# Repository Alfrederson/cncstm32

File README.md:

# cncstm32
CNC Base for Blue Pill

To be used with this port of GRBL for STM32F103F8T6: https://github.com/usbcnc/grbl or with Yaroslav's bugfixed and improved version:
https://github.com/yaroslavVl/6-AXIS-USBCNC-GRBL .

This board works with either 3d printer drivers or with external drivers using MKS-CD adapter.
An adapter could be made so that drivers that use a common 5V instead of a common GND for step/dir/enable (e.g: the aliexpress TB6600 drivers that come in a black aluminum enclosure) could be used as well.

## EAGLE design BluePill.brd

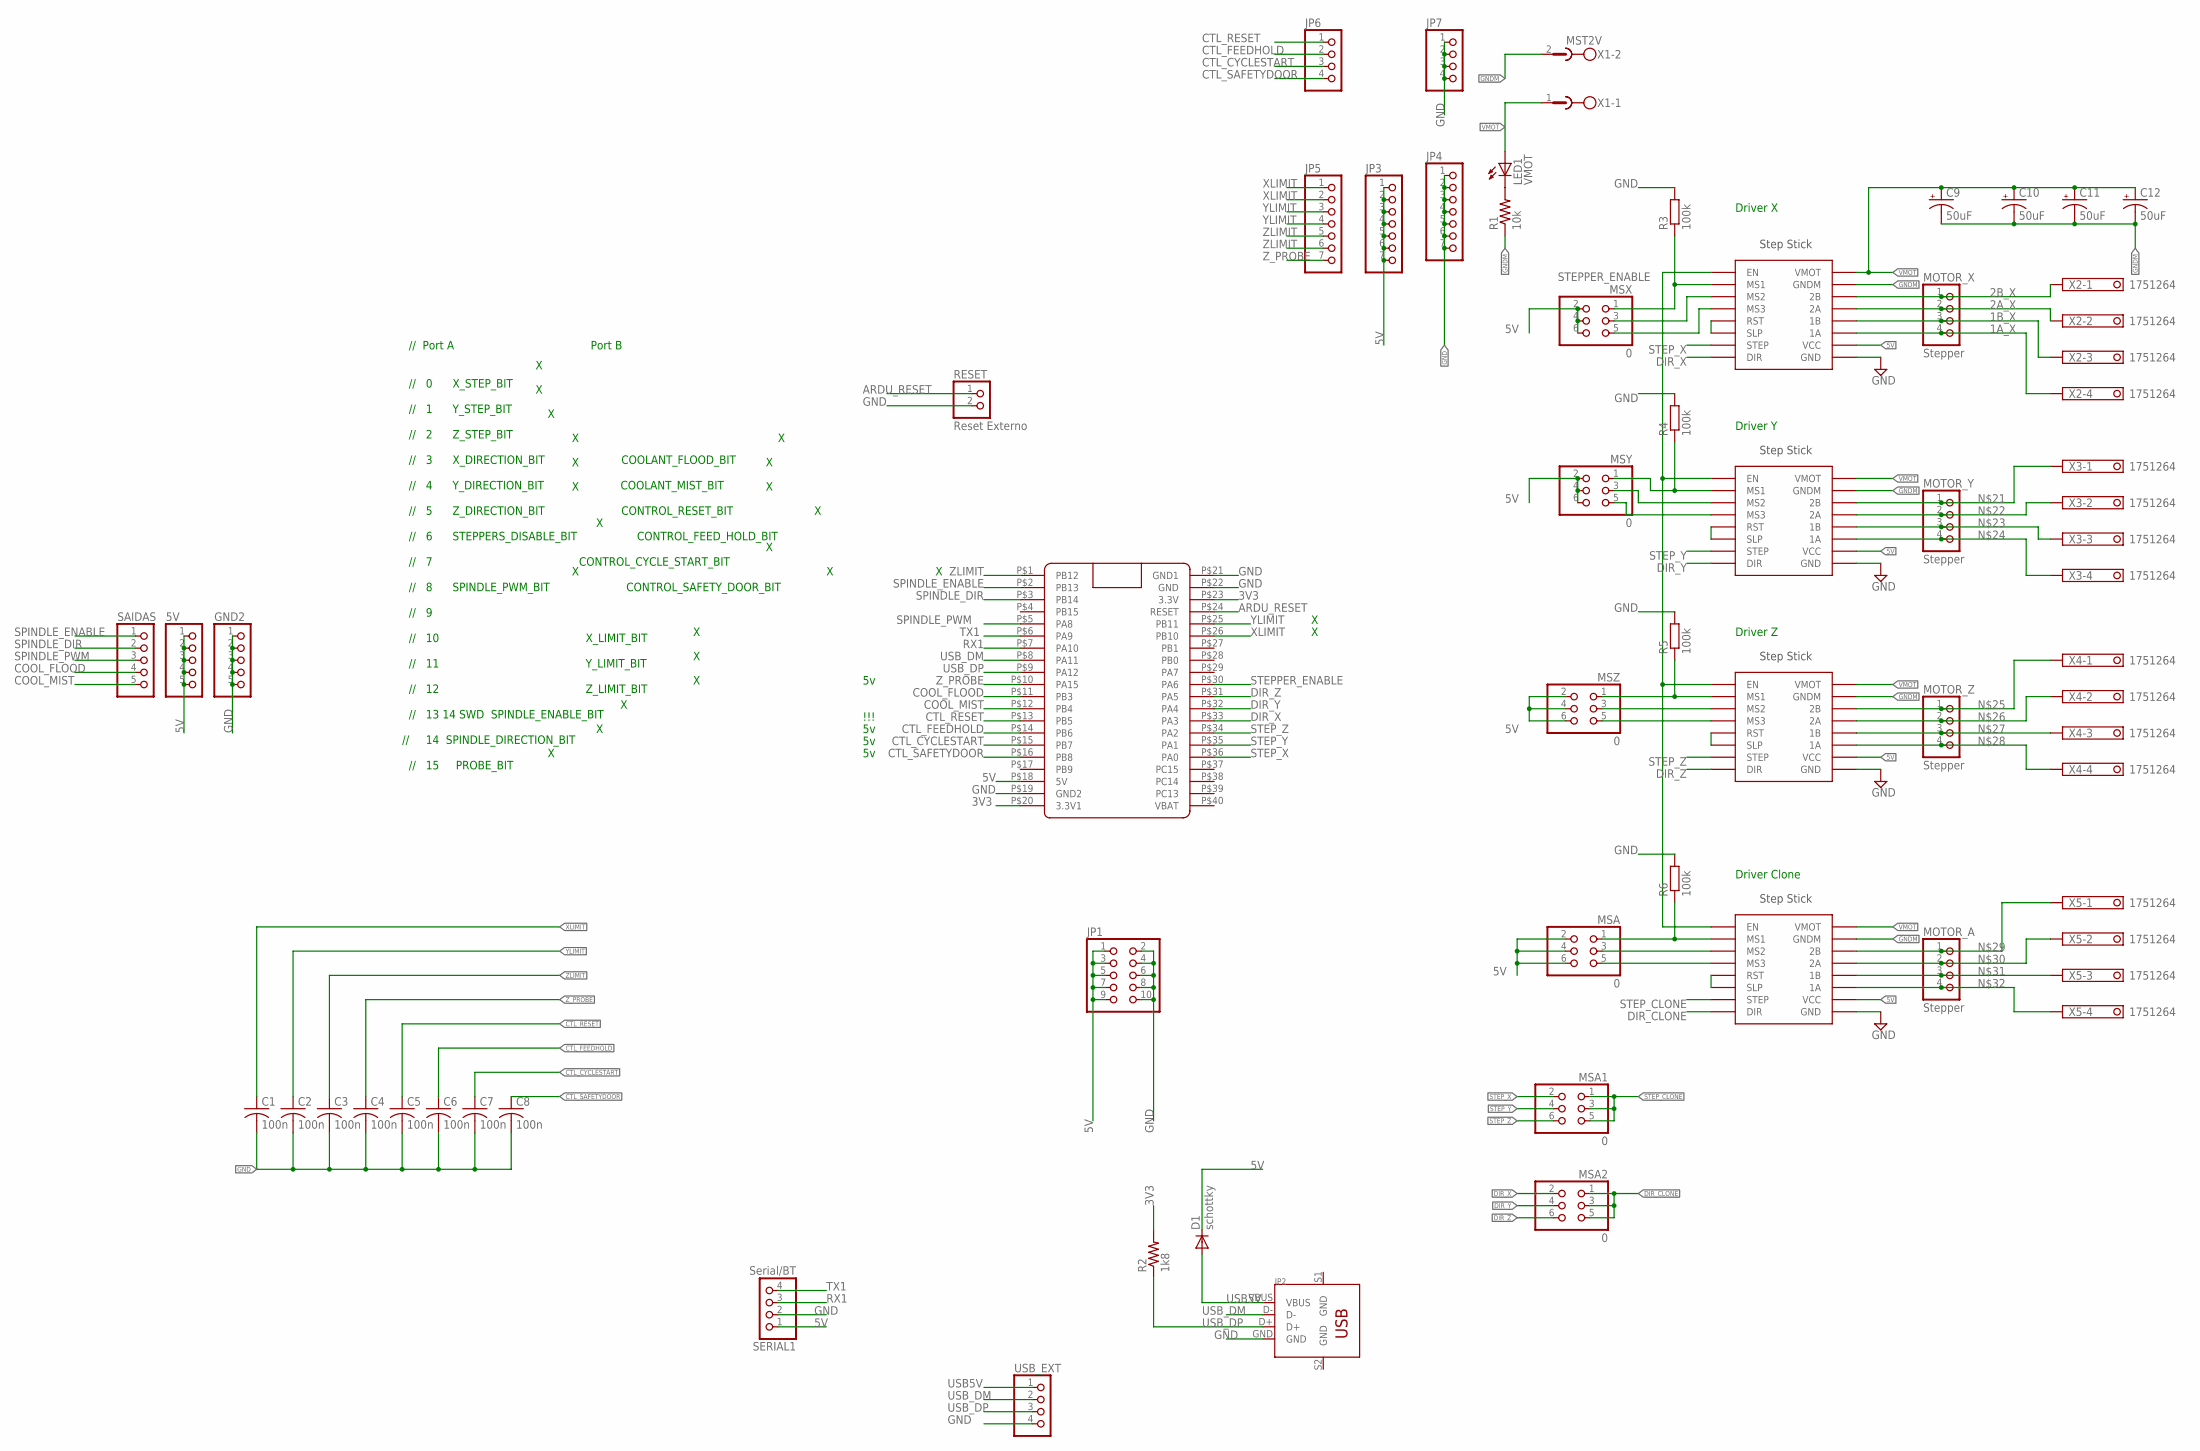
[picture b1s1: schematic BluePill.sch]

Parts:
5V: PINHD-1X5; 1X05
C1, C2, C3, C4, C5, C6, C7, C8: 100n; C0805K
C9, C10, C11, C12: 50uF; TT5D9L
D1: schottky; DO-214AC
DRIVER_CLONE: STEP-STICK
DRIVER_X: STEP-STICK
DRIVER_Y: STEP-STICK
DRIVER_Z: STEP-STICK
GND2: PINHD-1X5; 1X05
JP1: PINHD-2X5; 2X05
JP2: DIP-USB-B-TYPE-FMAL(4+2P-2.0-90D); USB4+2-2.5-90D-15.8X12MM
JP3, JP4, JP5: PINHD-1X7; 1X07
JP6, JP7: PINHD-1X4; 1X04
LED1: VMOT; CHIP-LED0805
MOTOR_A: Stepper; 1X04
MOTOR_X: Stepper; 1X04
MOTOR_Y: Stepper; 1X04
MOTOR_Z: Stepper; 1X04
MSA, MSA1, MSA2: 0; 2X03
MSX: 0; 2X03
MSY: 0; 2X03
MSZ: 0; 2X03
R1: 10k; M0805
R2: 1k8; R0805
R3, R4, R5, R6: 100k; R0805
RESET: Reset Externo; 1X02
SAIDAS: PINHD-1X5; 1X05
SERIAL1: Serial/BT; 1X04
U$1: BLUE_PILL
USB_EXT: PINHD-1X4; 1X04
X1: MST2V; MSTBV2
X2, X3, X4, X5: 1751264

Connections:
1A_X: DRIVER_X.1A, MOTOR_X.4, X2.4
1B_X: DRIVER_X.1B, MOTOR_X.3, X2.3
2A_X: DRIVER_X.2A, MOTOR_X.2, X2.2
2B_X: DRIVER_X.2B, MOTOR_X.1, X2.1
3V3: R2.2, U$1.P$20 (3.3V1), U$1.P$23 (3.3V)
5V: 5V.1, 5V.2, 5V.3, 5V.4, 5V.5, D1.C, DRIVER_CLONE.VCC, DRIVER_X.VCC, DRIVER_Y.VCC, DRIVER_Z.VCC, JP1.1, JP1.3, JP1.5, JP1.7, JP1.9, JP3.1, JP3.2, JP3.3, JP3.4, JP3.5, JP3.6, JP3.7, MSA.2, MSA.4, MSA.6, MSX.2, MSX.4, MSX.6, MSY.2, MSY.4, MSY.6, MSZ.2, MSZ.4, MSZ.6, SERIAL1.1, U$1.P$18 (5V)
AMS1: DRIVER_CLONE.MS1, MSA.1, R6.1
AMS2: DRIVER_CLONE.MS2, MSA.3
AMS3: DRIVER_CLONE.MS3, MSA.5
ARDU_RESET: RESET.1, U$1.P$24 (RESET)
COOL_FLOOD: SAIDAS.4, U$1.P$11 (PB3)
COOL_MIST: SAIDAS.5, U$1.P$12 (PB4)
CTL_CYCLESTART: C7.1, JP6.3, U$1.P$15 (PB7)
CTL_FEEDHOLD: C6.1, JP6.2, U$1.P$14 (PB6)
CTL_RESET: C5.1, JP6.1, U$1.P$13 (PB5)
CTL_SAFETYDOOR: C8.1, JP6.4, U$1.P$16 (PB8)
DIR_CLONE: DRIVER_CLONE.DIR, MSA2.1, MSA2.3, MSA2.5
DIR_X: DRIVER_X.DIR, MSA2.2, U$1.P$33 (PA3)
DIR_Y: DRIVER_Y.DIR, MSA2.4, U$1.P$32 (PA4)
DIR_Z: DRIVER_Z.DIR, MSA2.6, U$1.P$31 (PA5)
GND: C1.2, C2.2, C3.2, C4.2, C5.2, C6.2, C7.2, C8.2, DRIVER_CLONE.GND, DRIVER_X.GND, DRIVER_Y.GND, DRIVER_Z.GND, GND2.1, GND2.2, GND2.3, GND2.4, GND2.5, JP1.2, JP1.4, JP1.6, JP1.8, JP1.10, JP2.GND, JP4.1, JP4.2, JP4.3, JP4.4, JP4.5, JP4.6, JP4.7, JP7.1, JP7.2, JP7.3, JP7.4, R3.2, R4.2, R5.2, R6.2, RESET.2, SERIAL1.2, U$1.P$19 (GND2), U$1.P$21 (GND1), U$1.P$22 (GND), USB_EXT.4
GNDM: C9.-, C10.-, C11.-, C12.-, DRIVER_CLONE.GNDM, DRIVER_X.GNDM, DRIVER_Y.GNDM, DRIVER_Z.GNDM, R1.1, X1.2
MS1: DRIVER_X.MS1, MSX.1, R3.1
MS2: DRIVER_X.MS2, MSX.3
MS3: DRIVER_X.MS3, MSX.5
unnamed: DRIVER_X.RST, DRIVER_X.SLP
unnamed: DRIVER_Y.RST, DRIVER_Y.SLP
unnamed: DRIVER_Z.RST, DRIVER_Z.SLP
unnamed: DRIVER_CLONE.RST, DRIVER_CLONE.SLP
unnamed: DRIVER_Y.2B, MOTOR_Y.1, X3.1
unnamed: DRIVER_Y.2A, MOTOR_Y.2, X3.2
unnamed: DRIVER_Y.1B, MOTOR_Y.3, X3.3
unnamed: DRIVER_Y.1A, MOTOR_Y.4, X3.4
unnamed: DRIVER_Z.2B, MOTOR_Z.1, X4.1
unnamed: DRIVER_Z.2A, MOTOR_Z.2, X4.2
unnamed: DRIVER_Z.1B, MOTOR_Z.3, X4.3
unnamed: DRIVER_Z.1A, MOTOR_Z.4, X4.4
unnamed: DRIVER_CLONE.2B, MOTOR_A.1, X5.1
unnamed: DRIVER_CLONE.2A, MOTOR_A.2, X5.2
unnamed: DRIVER_CLONE.1B, MOTOR_A.3, X5.3
unnamed: DRIVER_CLONE.1A, MOTOR_A.4, X5.4
unnamed: LED1.C, R1.2
RX1: SERIAL1.3, U$1.P$7 (PA10)
SPINDLE_DIR: SAIDAS.2, U$1.P$3 (PB14)
SPINDLE_ENABLE: SAIDAS.1, U$1.P$2 (PB13)
SPINDLE_PWM: SAIDAS.3, U$1.P$5 (PA8)
STEPPER_ENABLE: DRIVER_CLONE.EN, DRIVER_X.EN, DRIVER_Y.EN, DRIVER_Z.EN, U$1.P$30 (PA6)
STEP_CLONE: DRIVER_CLONE.SPT (STEP), MSA1.1, MSA1.3, MSA1.5
STEP_X: DRIVER_X.SPT (STEP), MSA1.2, U$1.P$36 (PA0)
STEP_Y: DRIVER_Y.SPT (STEP), MSA1.4, U$1.P$35 (PA1)
STEP_Z: DRIVER_Z.SPT (STEP), MSA1.6, U$1.P$34 (PA2)
TX1: SERIAL1.4, U$1.P$6 (PA9)
USB5V: D1.A, JP2.VBUS, USB_EXT.1
USB_DM: JP2.D-, U$1.P$8 (PA11), USB_EXT.2
USB_DP: JP2.D+, R2.1, U$1.P$9 (PA12), USB_EXT.3
VMOT: C9.+, C10.+, C11.+, C12.+, DRIVER_CLONE.VMOT, DRIVER_X.VMOT, DRIVER_Y.VMOT, DRIVER_Z.VMOT, LED1.A, X1.1
XLIMIT: C1.1, JP5.1, JP5.2, U$1.P$26 (PB10)
YLIMIT: C2.1, JP5.3, JP5.4, U$1.P$25 (PB11)
YMS1: DRIVER_Y.MS1, MSY.1, R4.1
YMS2: DRIVER_Y.MS2, MSY.3
YMS3: DRIVER_Y.MS3, MSY.5
ZLIMIT: C3.1, JP5.5, JP5.6, U$1.P$1 (PB12)
ZMS1: DRIVER_Z.MS1, MSZ.1, R5.1
ZMS2: DRIVER_Z.MS2, MSZ.3
ZMS3: DRIVER_Z.MS3, MSZ.5
Z_PROBE: C4.1, JP5.7, U$1.P$10 (PA15)

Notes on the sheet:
Driver X
Driver Y
Driver Z
Driver Clone
// Port A Port B // 0 X_STEP_BIT // 1 Y_STEP_BIT // 2 Z_STEP_BIT // 3 X_DIRECTION_BIT COOLANT_FLOOD_BIT // 4 Y_DIRECTION_BIT COOLANT_MIST_BIT // 5 Z_DIRECTION_BIT CONTROL_RESET_BIT // 6 STEPPERS_DISABLE_BIT CONTROL_FEED_HOLD_BIT // 7 CONTROL_CYCLE_START_BIT // 8 SPINDLE_PWM_BIT CONTROL_SAFETY_DOOR_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
!!!

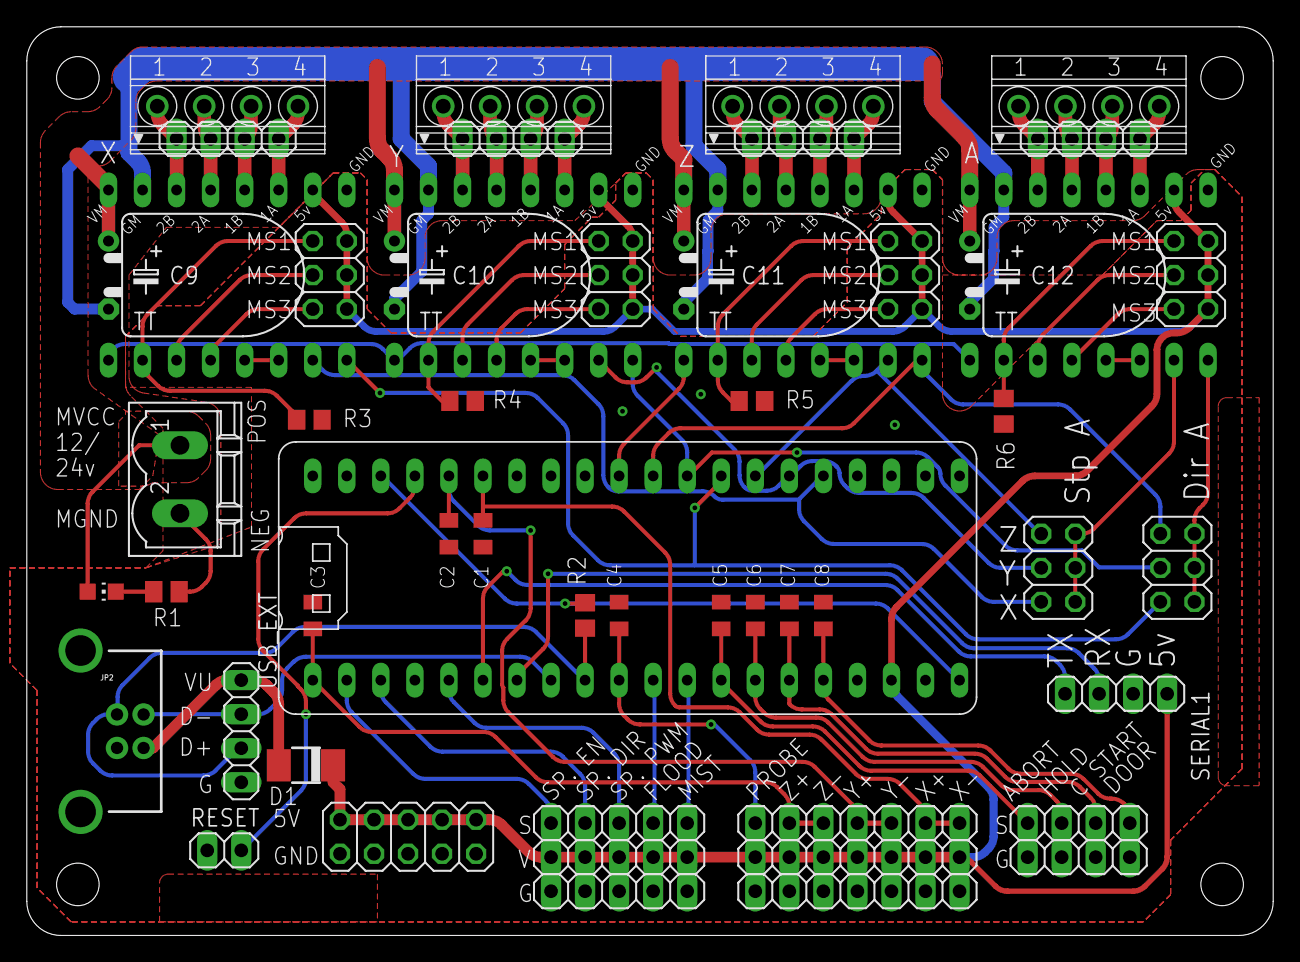
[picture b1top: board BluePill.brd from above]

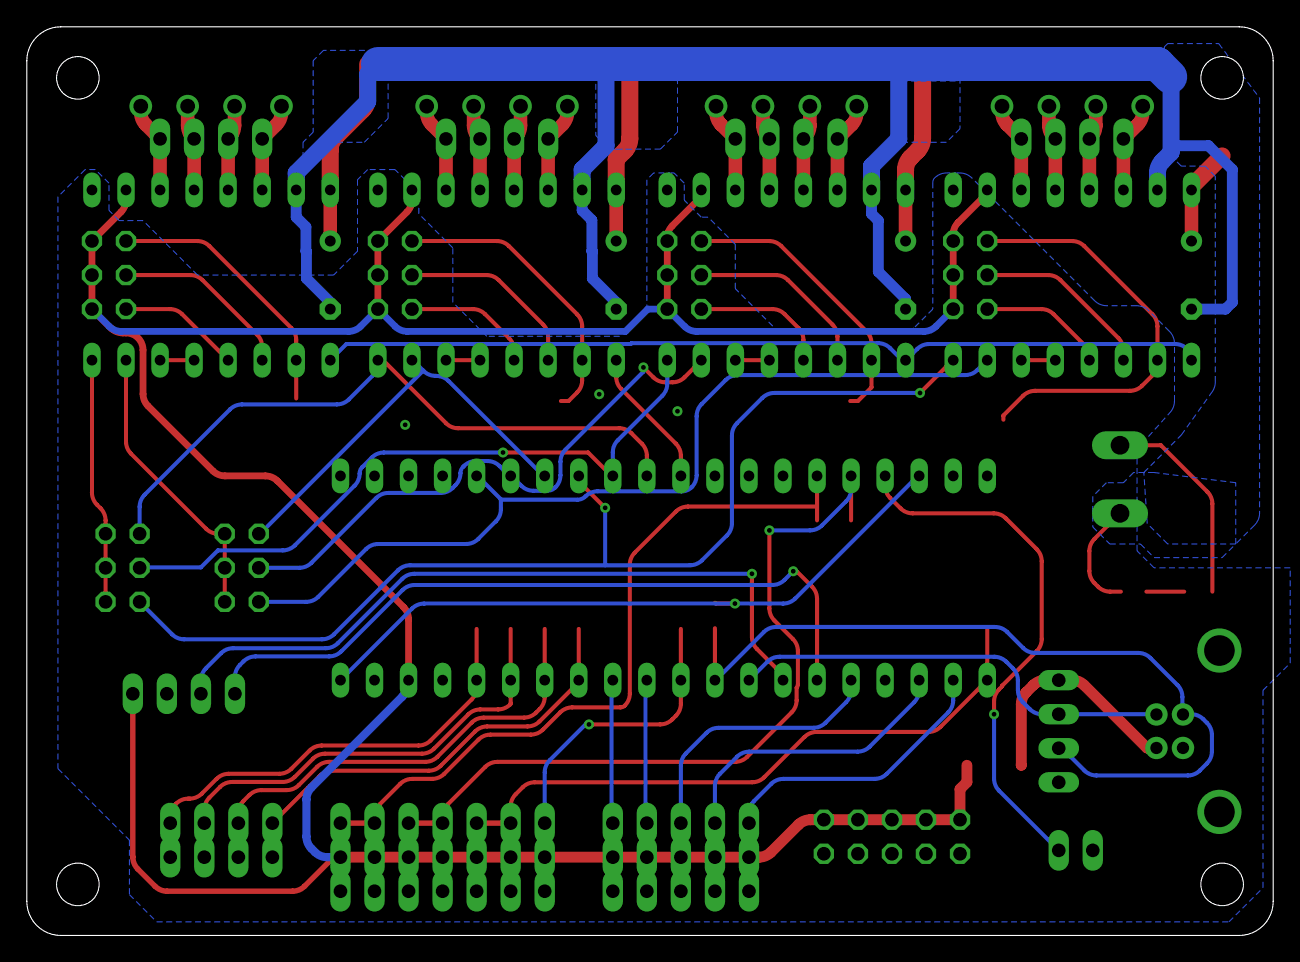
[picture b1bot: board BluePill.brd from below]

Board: 2 copper layers, 93.0 x 67.8 mm, 53 parts (4 on the bottom side), 66 nets.

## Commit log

2018-11-07 Add files via upload
    Primeira revisão
2019-02-24 Create gerber
